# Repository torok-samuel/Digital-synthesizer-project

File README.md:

# Digital-synthesizer-project
Digital synthesizer project for university thesis.

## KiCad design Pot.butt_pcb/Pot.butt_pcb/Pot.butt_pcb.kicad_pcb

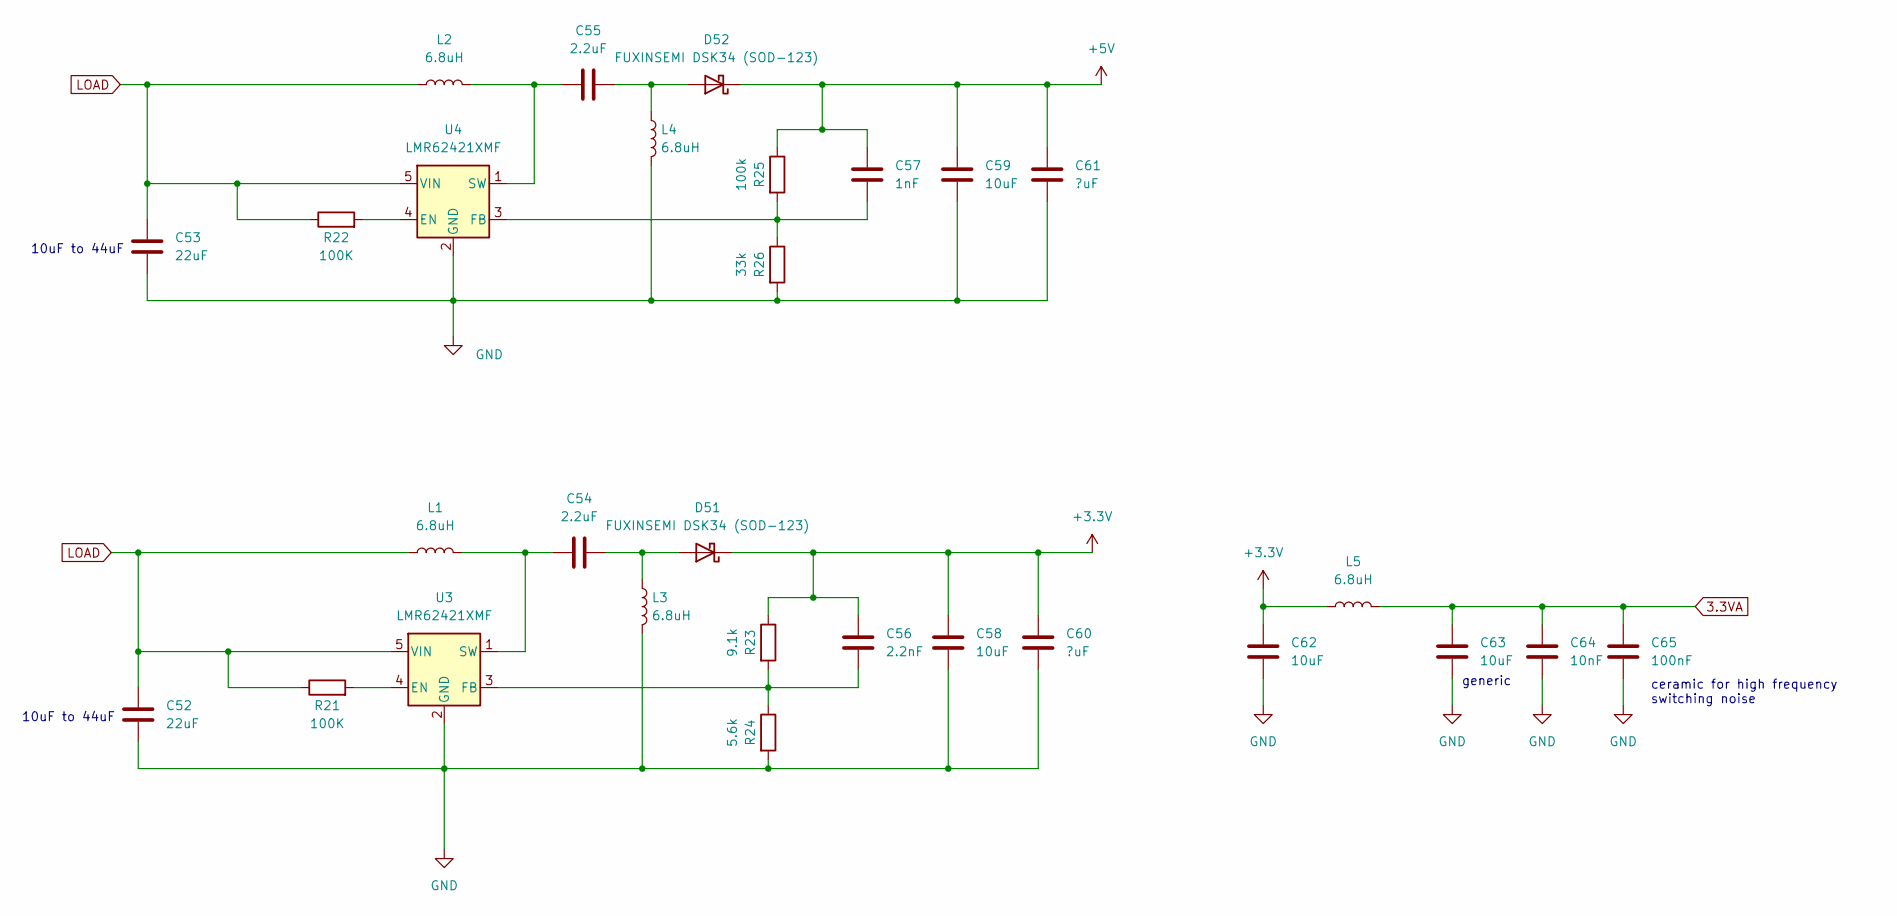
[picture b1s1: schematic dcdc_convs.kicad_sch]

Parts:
C52, C53: 22uF; C_0805_2012Metric_Pad1.18x1.45mm_HandSolder
C54, C55: 2.2uF; C_0805_2012Metric_Pad1.18x1.45mm_HandSolder
C56: 2.2nF; C_0805_2012Metric_Pad1.18x1.45mm_HandSolder
C57: 1nF; C_0805_2012Metric_Pad1.18x1.45mm_HandSolder
C58, C59, C62, C63: 10uF; C_0805_2012Metric_Pad1.18x1.45mm_HandSolder
C60, C61: ?uF; C_0805_2012Metric_Pad1.18x1.45mm_HandSolder
C64: 10nF; C_0805_2012Metric_Pad1.18x1.45mm_HandSolder
C65: 100nF; C_0805_2012Metric_Pad1.18x1.45mm_HandSolder
D51, D52: FUXINSEMI DSK34 (SOD-123); D_SOD-123
L1, L2, L3, L4, L5: 6.8uH; inductor_koherelec
R21, R22: 100K; R_0805_2012Metric_Pad1.20x1.40mm_HandSolder
R23: 9.1k; R_0805_2012Metric_Pad1.20x1.40mm_HandSolder
R24: 5.6k; R_0805_2012Metric_Pad1.20x1.40mm_HandSolder
R25: 100k; R_0805_2012Metric_Pad1.20x1.40mm_HandSolder
R26: 33k; R_0805_2012Metric_Pad1.20x1.40mm_HandSolder
U3, U4: LMR62421XMF; SOT-23-5

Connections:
3.3VA: C63.1, C64.1, C65.1, L5.2; also elsewhere on the board
+3V3: C56.1, C58.1, C60.1, C62.1, D51.1 (K), L5.1, R23.1; also elsewhere on the board
+5V: C57.1, C59.1, C61.1, D52.1 (K), R25.1; also elsewhere on the board
GND: C52.2, C53.2, C58.2, C59.2, C60.2, C61.2, C62.2, C63.2, C64.2, C65.2, L3.2, L4.2, R24.2, R26.2, U3.2 (GND), U4.2 (GND); also elsewhere on the board
LOAD: C52.1, C53.1, L1.1, L2.1, R21.1, R22.1, U3.5 (VIN), U4.5 (VIN); also elsewhere on the board
unnamed: C54.1, L1.2, U3.1 (SW)
unnamed: C54.2, D51.2 (A), L3.1
unnamed: C55.1, L2.2, U4.1 (SW)
unnamed: C55.2, D52.2 (A), L4.1
unnamed: C56.2, R23.2, R24.1, U3.3 (FB)
unnamed: C57.2, R25.2, R26.1, U4.3 (FB)
unnamed: R21.2, U3.4 (EN)
unnamed: R22.2, U4.4 (EN)

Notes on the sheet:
10uF to 44uF
generic
ceramic for high frequency switching noise

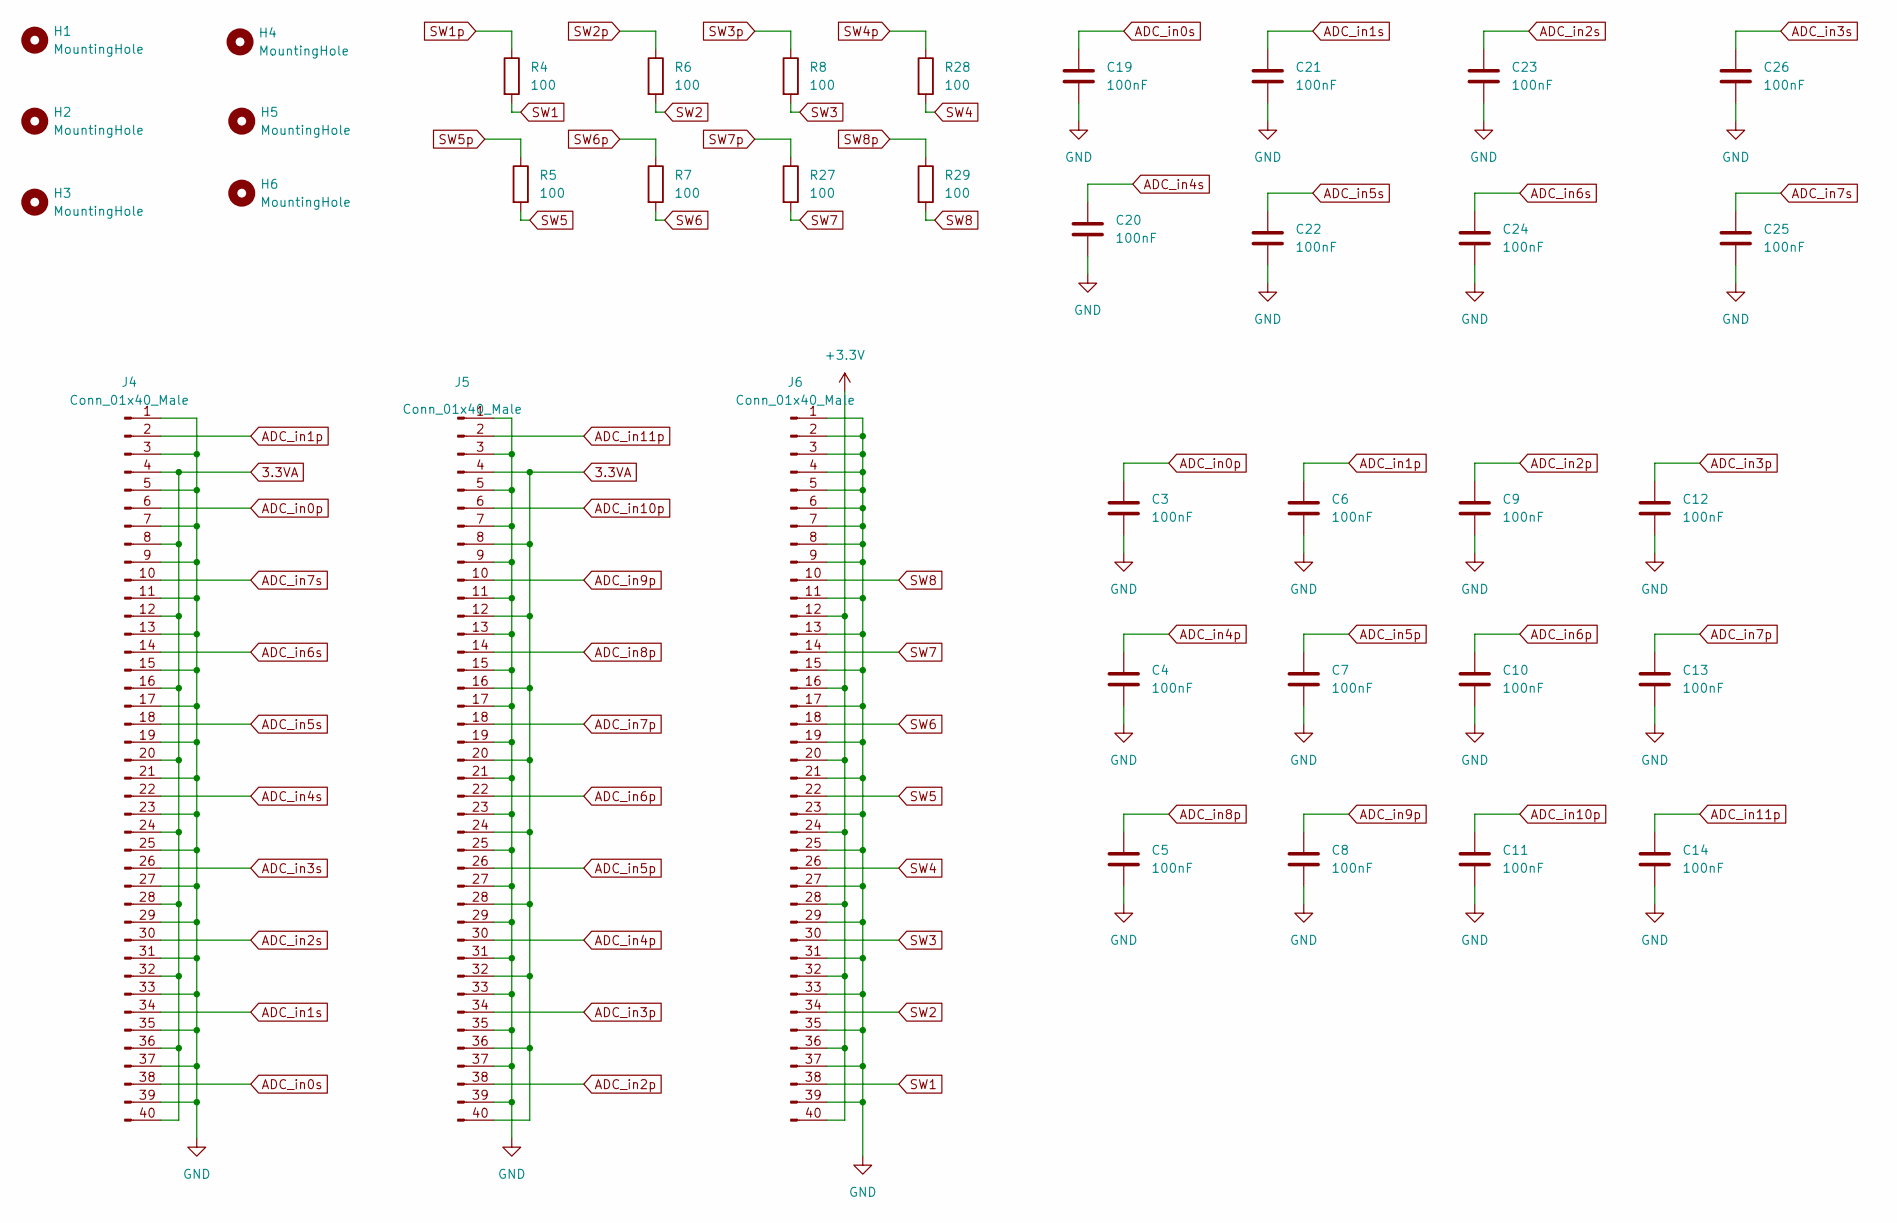
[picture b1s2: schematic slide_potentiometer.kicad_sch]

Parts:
C3, C4, C5, C6, C7, C8, C9, C10, C11, C12, C13, C14, C19, C20, C21, C22, C23, C24, C25, C26: 100nF; C_0805_2012Metric_Pad1.18x1.45mm_HandSolder
H1, H2, H3, H4, H5, H6: MountingHole; MountingHole_3.2mm_M3_Pad_Via
J4, J5, J6: Conn_01x40_Male; IDC-Header_2x20_P2.54mm_Vertical
R4, R5, R6, R7, R8, R27, R28, R29: 100; R_0805_2012Metric_Pad1.20x1.40mm_HandSolder

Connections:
3.3VA: J4.4, J4.8, J4.12, J4.16, J4.20, J4.24, J4.28, J4.32, J4.36, J4.40, J5.4, J5.8, J5.12, J5.16, J5.20, J5.24, J5.28, J5.32, J5.36, J5.40; also elsewhere on the board
+3V3: J6.12, J6.16, J6.20, J6.24, J6.28, J6.32, J6.36, J6.40; also elsewhere on the board
ADC_in0p: C3.1, J4.6; also elsewhere on the board
ADC_in0s: C19.1, J4.38; also elsewhere on the board
ADC_in1p: C6.1, J4.2; also elsewhere on the board
ADC_in1s: C21.1, J4.34; also elsewhere on the board
ADC_in2p: C9.1, J5.38; also elsewhere on the board
ADC_in2s: C23.1, J4.30; also elsewhere on the board
ADC_in3p: C12.1, J5.34; also elsewhere on the board
ADC_in3s: C26.1, J4.26; also elsewhere on the board
ADC_in4p: C4.1, J5.30; also elsewhere on the board
ADC_in4s: C20.1, J4.22; also elsewhere on the board
ADC_in5p: C7.1, J5.26; also elsewhere on the board
ADC_in5s: C22.1, J4.18; also elsewhere on the board
ADC_in6p: C10.1, J5.22; also elsewhere on the board
ADC_in6s: C24.1, J4.14; also elsewhere on the board
ADC_in7p: C13.1, J5.18; also elsewhere on the board
ADC_in7s: C25.1, J4.10; also elsewhere on the board
ADC_in8p: C5.1, J5.14; also elsewhere on the board
ADC_in9p: C8.1, J5.10; also elsewhere on the board
ADC_in10p: C11.1, J5.6; also elsewhere on the board
ADC_in11p: C14.1, J5.2; also elsewhere on the board
GND: C3.2, C4.2, C5.2, C6.2, C7.2, C8.2, C9.2, C10.2, C11.2, C12.2, C13.2, C14.2, C19.2, C20.2, C21.2, C22.2, C23.2, C24.2, C25.2, C26.2, J4.1, J4.3, J4.5, J4.7, J4.9, J4.11, J4.13, J4.15, J4.17, J4.19, J4.21, J4.23, J4.25, J4.27, J4.29, J4.31, J4.33, J4.35, J4.37, J4.39, J5.1, J5.3, J5.5, J5.7, J5.9, J5.11, J5.13, J5.15, J5.17, J5.19, J5.21, J5.23, J5.25, J5.27, J5.29, J5.31, J5.33, J5.35, J5.37, J5.39, J6.1, J6.2, J6.3, J6.4, J6.5, J6.6, J6.7, J6.8, J6.9, J6.11, J6.13, J6.15, J6.17, J6.19, J6.21, J6.23, J6.25, J6.27, J6.29, J6.31, J6.33, J6.35, J6.37, J6.39; also elsewhere on the board
SW1: J6.38, R4.2
SW1p: R4.1; also elsewhere on the board
SW2: J6.34, R6.2
SW2p: R6.1; also elsewhere on the board
SW3: J6.30, R8.2
SW3p: R8.1; also elsewhere on the board
SW4: J6.26, R28.2
SW4p: R28.1; also elsewhere on the board
SW5: J6.22, R5.2
SW5p: R5.1; also elsewhere on the board
SW6: J6.18, R7.2
SW6p: R7.1; also elsewhere on the board
SW7: J6.14, R27.2
SW7p: R27.1; also elsewhere on the board
SW8: J6.10, R29.2
SW8p: R29.1; also elsewhere on the board

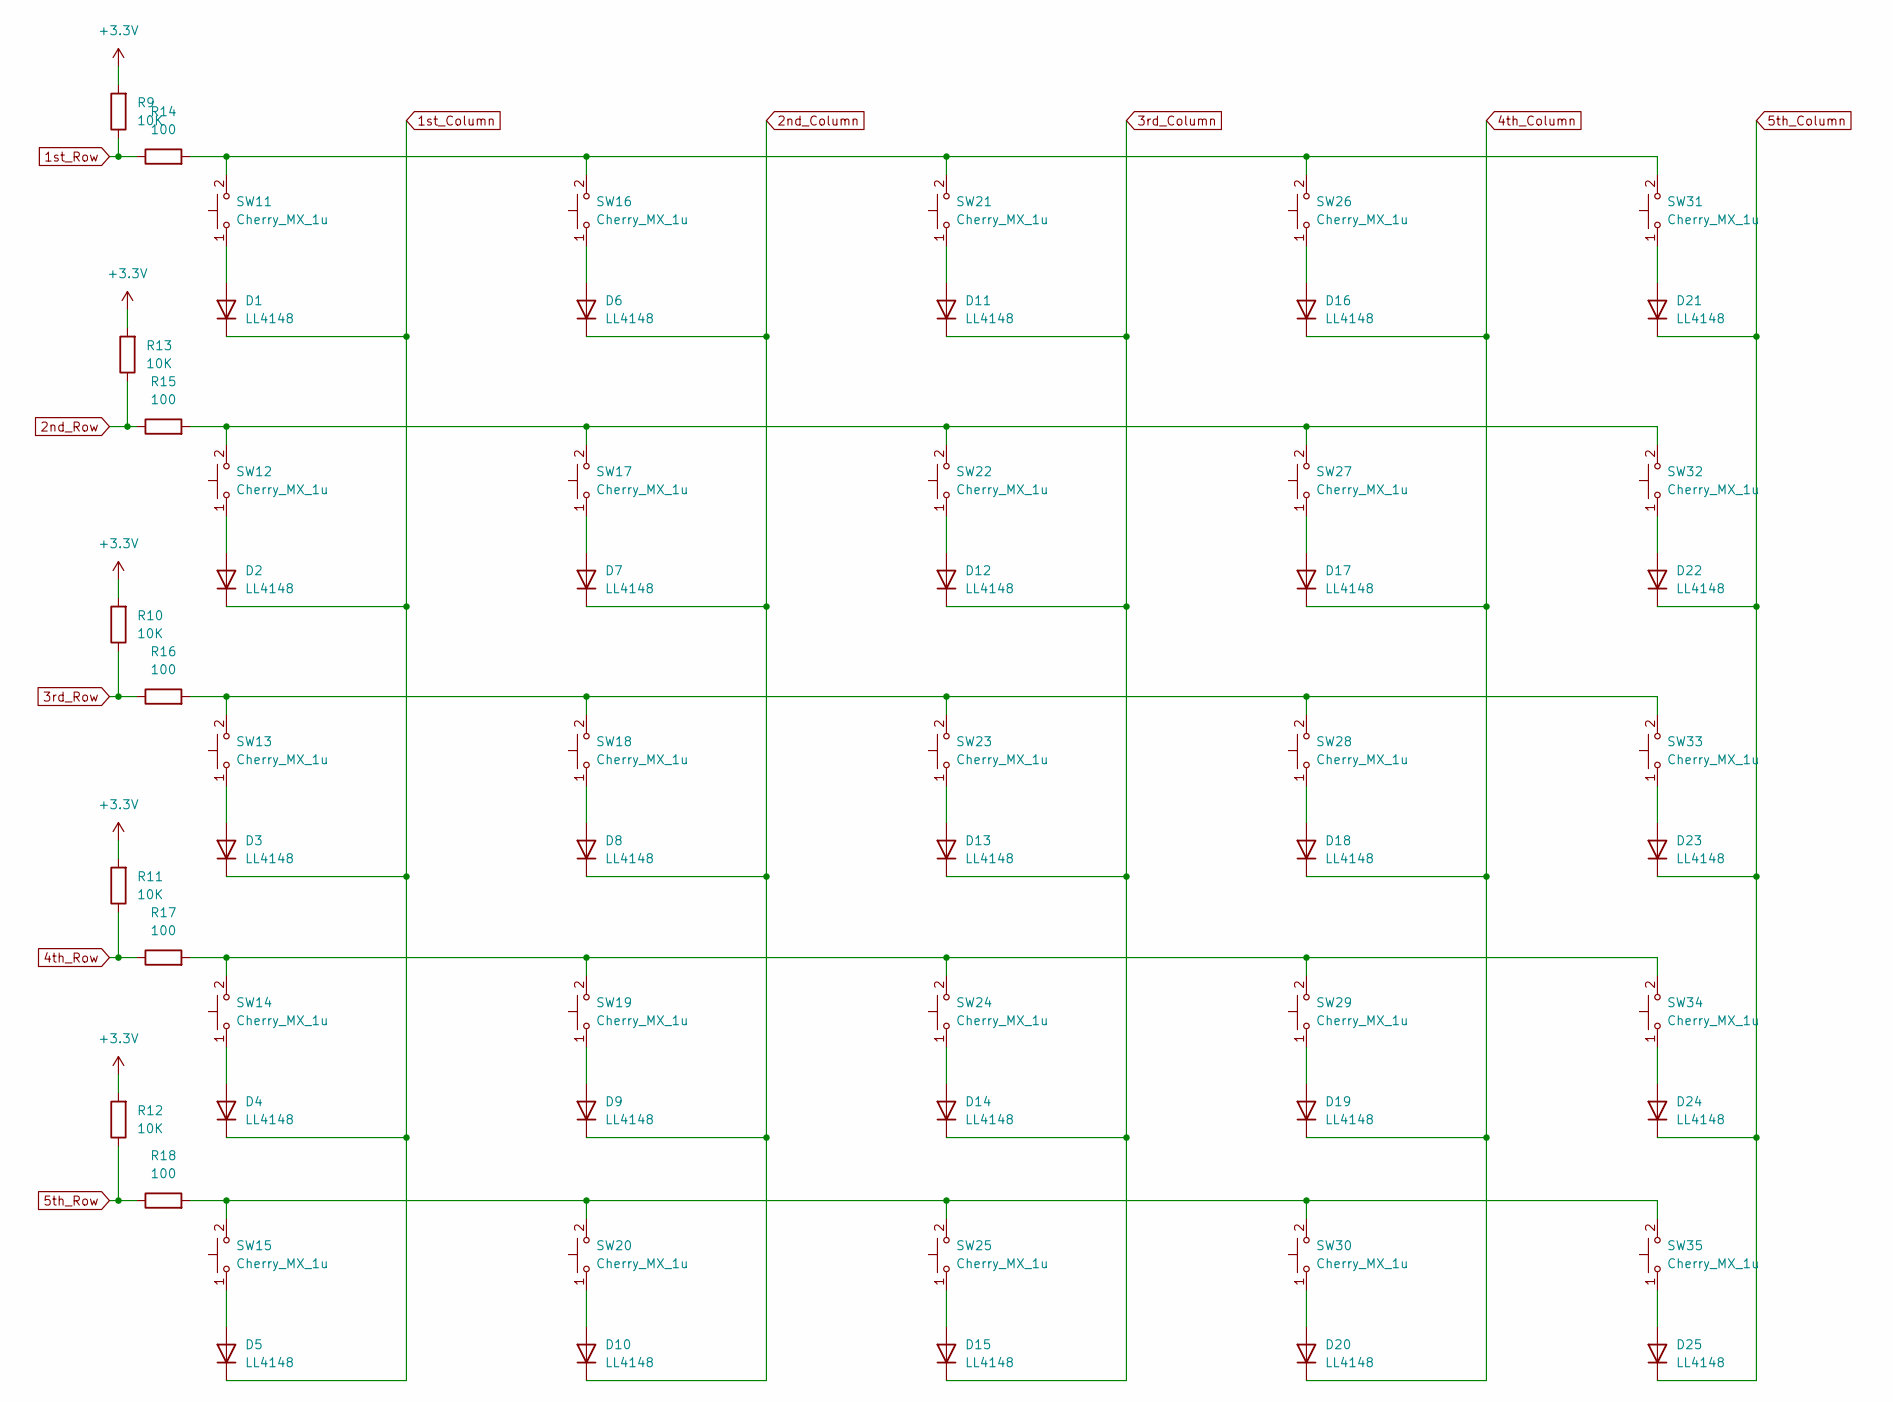
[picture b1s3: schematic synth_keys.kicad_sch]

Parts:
D1, D2, D3, D4, D5, D6, D7, D8, D9, D10, D11, D12, D13, D14, D15, D16, D17, D18, D19, D20, D21, D22, D23, D24, D25: LL4148; D_MiniMELF
R9, R10, R11, R12, R13: 10K; R_0805_2012Metric_Pad1.20x1.40mm_HandSolder
R14, R15, R16, R17, R18: 100; R_0805_2012Metric_Pad1.20x1.40mm_HandSolder
SW11, SW12, SW13, SW14, SW15, SW16, SW17, SW18, SW19, SW20, SW21, SW22, SW23, SW24, SW25, SW26, SW27, SW28, SW29, SW30, SW31, SW32, SW33, SW34, SW35: Cherry_MX_1u; SW_Cherry_MX_PCB_1.00u

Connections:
1st_Column: D1.1 (K), D2.1 (K), D3.1 (K), D4.1 (K), D5.1 (K); also elsewhere on the board
1st_Row: R9.1, R14.1; also elsewhere on the board
2nd_Column: D6.1 (K), D7.1 (K), D8.1 (K), D9.1 (K), D10.1 (K); also elsewhere on the board
2nd_Row: R13.1, R15.1; also elsewhere on the board
3rd_Column: D11.1 (K), D12.1 (K), D13.1 (K), D14.1 (K), D15.1 (K); also elsewhere on the board
3rd_Row: R10.1, R16.1; also elsewhere on the board
4th_Column: D16.1 (K), D17.1 (K), D18.1 (K), D19.1 (K), D20.1 (K); also elsewhere on the board
4th_Row: R11.1, R17.1; also elsewhere on the board
5th_Column: D21.1 (K), D22.1 (K), D23.1 (K), D24.1 (K), D25.1 (K); also elsewhere on the board
5th_Row: R12.1, R18.1; also elsewhere on the board
+3V3: R9.2, R10.2, R11.2, R12.2, R13.2; also elsewhere on the board
unnamed: D1.2 (A), SW11.1
unnamed: D2.2 (A), SW12.1
unnamed: D3.2 (A), SW13.1
unnamed: D4.2 (A), SW14.1
unnamed: D5.2 (A), SW15.1
unnamed: D6.2 (A), SW16.1
unnamed: D7.2 (A), SW17.1
unnamed: D8.2 (A), SW18.1
unnamed: D9.2 (A), SW19.1
unnamed: D10.2 (A), SW20.1
unnamed: D11.2 (A), SW21.1
unnamed: D12.2 (A), SW22.1
unnamed: D13.2 (A), SW23.1
unnamed: D14.2 (A), SW24.1
unnamed: D15.2 (A), SW25.1
unnamed: D16.2 (A), SW26.1
unnamed: D17.2 (A), SW27.1
unnamed: D18.2 (A), SW28.1
unnamed: D19.2 (A), SW29.1
unnamed: D20.2 (A), SW30.1
unnamed: D21.2 (A), SW31.1
unnamed: D22.2 (A), SW32.1
unnamed: D23.2 (A), SW33.1
unnamed: D24.2 (A), SW34.1
unnamed: D25.2 (A), SW35.1
unnamed: R14.2, SW11.2, SW16.2, SW21.2, SW26.2, SW31.2
unnamed: R15.2, SW12.2, SW17.2, SW22.2, SW27.2, SW32.2
unnamed: R16.2, SW13.2, SW18.2, SW23.2, SW28.2, SW33.2
unnamed: R17.2, SW14.2, SW19.2, SW24.2, SW29.2, SW34.2
unnamed: R18.2, SW15.2, SW20.2, SW25.2, SW30.2, SW35.2

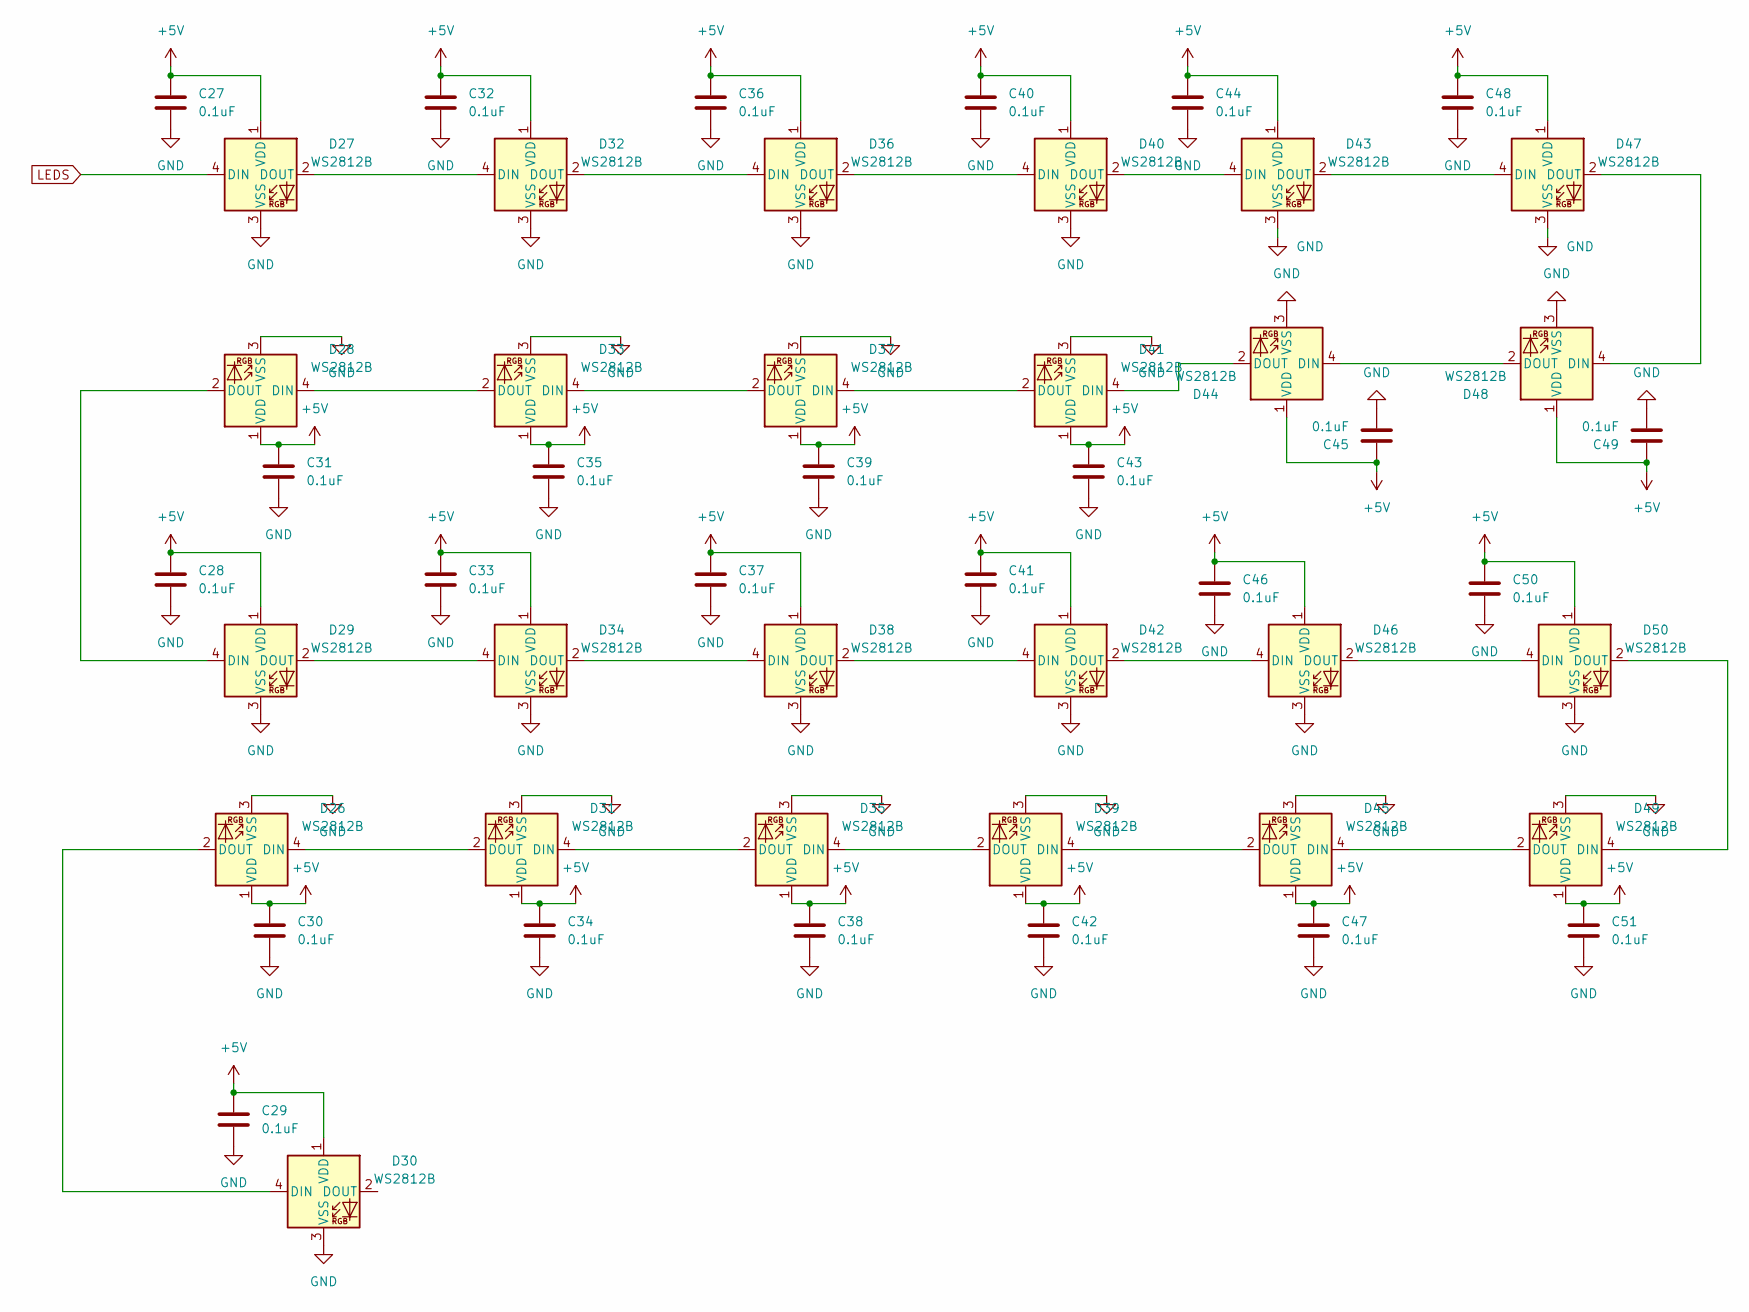
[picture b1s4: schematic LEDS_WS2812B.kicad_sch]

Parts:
C27, C28, C29, C30, C31, C32, C33, C34, C35, C36, C37, C38, C39, C40, C41, C42, C43, C44, C45, C46, C47, C48, C49, C50, C51: 0.1uF; C_0805_2012Metric_Pad1.18x1.45mm_HandSolder
D26, D27, D28, D29, D30, D31, D32, D33, D34, D35, D36, D37, D38, D39, D40, D41, D42, D43, D44, D45, D46, D47, D48, D49, D50: WS2812B; LED_WS2812B_PLCC4_5.0x5.0mm_P3.2mm

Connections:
+5V: C27.1, C28.1, C29.1, C30.1, C31.1, C32.1, C33.1, C34.1, C35.1, C36.1, C37.1, C38.1, C39.1, C40.1, C41.1, C42.1, C43.1, C44.1, C45.1, C46.1, C47.1, C48.1, C49.1, C50.1, C51.1, D26.1 (VDD), D27.1 (VDD), D28.1 (VDD), D29.1 (VDD), D30.1 (VDD), D31.1 (VDD), D32.1 (VDD), D33.1 (VDD), D34.1 (VDD), D35.1 (VDD), D36.1 (VDD), D37.1 (VDD), D38.1 (VDD), D39.1 (VDD), D40.1 (VDD), D41.1 (VDD), D42.1 (VDD), D43.1 (VDD), D44.1 (VDD), D45.1 (VDD), D46.1 (VDD), D47.1 (VDD), D48.1 (VDD), D49.1 (VDD), D50.1 (VDD); also elsewhere on the board
GND: C27.2, C28.2, C29.2, C30.2, C31.2, C32.2, C33.2, C34.2, C35.2, C36.2, C37.2, C38.2, C39.2, C40.2, C41.2, C42.2, C43.2, C44.2, C45.2, C46.2, C47.2, C48.2, C49.2, C50.2, C51.2, D26.3 (VSS), D27.3 (VSS), D28.3 (VSS), D29.3 (VSS), D30.3 (VSS), D31.3 (VSS), D32.3 (VSS), D33.3 (VSS), D34.3 (VSS), D35.3 (VSS), D36.3 (VSS), D37.3 (VSS), D38.3 (VSS), D39.3 (VSS), D40.3 (VSS), D41.3 (VSS), D42.3 (VSS), D43.3 (VSS), D44.3 (VSS), D45.3 (VSS), D46.3 (VSS), D47.3 (VSS), D48.3 (VSS), D49.3 (VSS), D50.3 (VSS); also elsewhere on the board
LEDS: D27.4 (DIN); also elsewhere on the board
unnamed: D26.2 (DOUT), D30.4 (DIN)
unnamed: D26.4 (DIN), D31.2 (DOUT)
unnamed: D27.2 (DOUT), D32.4 (DIN)
unnamed: D28.2 (DOUT), D29.4 (DIN)
unnamed: D28.4 (DIN), D33.2 (DOUT)
unnamed: D29.2 (DOUT), D34.4 (DIN)
unnamed: D31.4 (DIN), D35.2 (DOUT)
unnamed: D32.2 (DOUT), D36.4 (DIN)
unnamed: D33.4 (DIN), D37.2 (DOUT)
unnamed: D34.2 (DOUT), D38.4 (DIN)
unnamed: D35.4 (DIN), D39.2 (DOUT)
unnamed: D36.2 (DOUT), D40.4 (DIN)
unnamed: D37.4 (DIN), D41.2 (DOUT)
unnamed: D38.2 (DOUT), D42.4 (DIN)
unnamed: D39.4 (DIN), D45.2 (DOUT)
unnamed: D40.2 (DOUT), D43.4 (DIN)
unnamed: D41.4 (DIN), D44.2 (DOUT)
unnamed: D42.2 (DOUT), D46.4 (DIN)
unnamed: D43.2 (DOUT), D47.4 (DIN)
unnamed: D44.4 (DIN), D48.2 (DOUT)
unnamed: D45.4 (DIN), D49.2 (DOUT)
unnamed: D46.2 (DOUT), D50.4 (DIN)
unnamed: D47.2 (DOUT), D48.4 (DIN)
unnamed: D49.4 (DIN), D50.2 (DOUT)

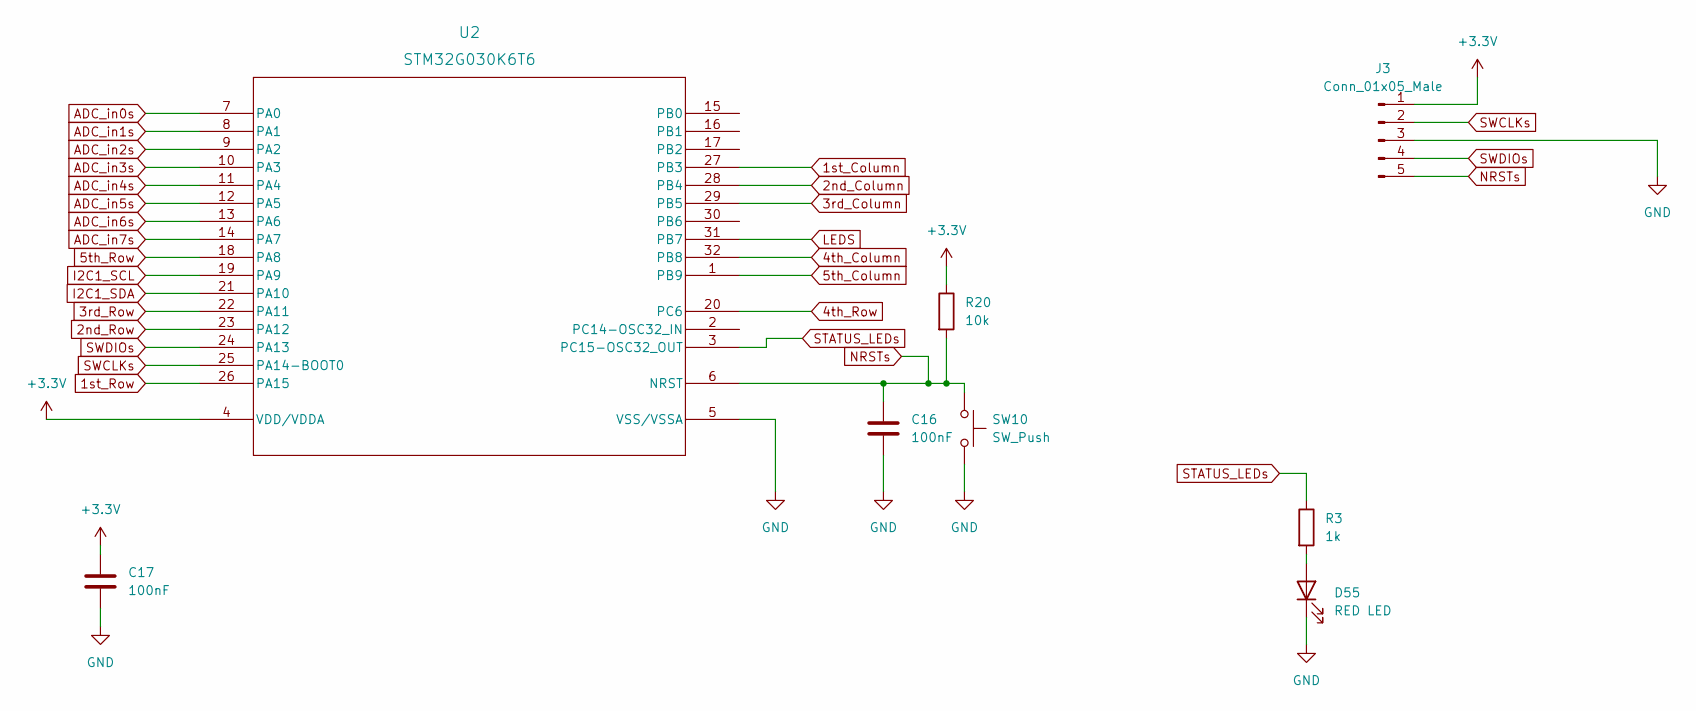
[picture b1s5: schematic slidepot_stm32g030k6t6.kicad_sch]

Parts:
C16, C17: 100nF; C_0805_2012Metric_Pad1.18x1.45mm_HandSolder
D55: RED LED; LED_0805_2012Metric_Pad1.15x1.40mm_HandSolder
J3: Conn_01x05_Male; PinSocket_1x05_P2.54mm_Horizontal
R3: 1k; R_0805_2012Metric_Pad1.20x1.40mm_HandSolder
R20: 10k; R_0805_2012Metric_Pad1.20x1.40mm_HandSolder
SW10: SW_Push; ROCPU Switches TP10721645
U2: STM32G030K6T6; LQFP-32

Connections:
1st_Column: U2.27 (PB3); also elsewhere on the board
1st_Row: U2.26 (PA15); also elsewhere on the board
2nd_Column: U2.28 (PB4); also elsewhere on the board
2nd_Row: U2.23 (PA12); also elsewhere on the board
3rd_Column: U2.29 (PB5); also elsewhere on the board
3rd_Row: U2.22 (PA11); also elsewhere on the board
4th_Column: U2.32 (PB8); also elsewhere on the board
4th_Row: U2.20 (PC6); also elsewhere on the board
5th_Column: U2.1 (PB9); also elsewhere on the board
5th_Row: U2.18 (PA8); also elsewhere on the board
+3V3: C17.1, J3.1, R20.1, U2.4 (VDD/VDDA); also elsewhere on the board
ADC_in0s: U2.7 (PA0); also elsewhere on the board
ADC_in1s: U2.8 (PA1); also elsewhere on the board
ADC_in2s: U2.9 (PA2); also elsewhere on the board
ADC_in3s: U2.10 (PA3); also elsewhere on the board
ADC_in4s: U2.11 (PA4); also elsewhere on the board
ADC_in5s: U2.12 (PA5); also elsewhere on the board
ADC_in6s: U2.13 (PA6); also elsewhere on the board
ADC_in7s: U2.14 (PA7); also elsewhere on the board
GND: C16.2, C17.2, D55.1 (K), J3.3, SW10.2, U2.5 (VSS/VSSA); also elsewhere on the board
I2C1_SCL: U2.19 (PA9); also elsewhere on the board
I2C1_SDA: U2.21 (PA10); also elsewhere on the board
LEDS: U2.31 (PB7); also elsewhere on the board
NRSTs: C16.1, J3.5, R20.2, SW10.1, U2.6 (NRST)
unnamed: D55.2 (A), R3.2
STATUS_LEDs: R3.1, U2.3 (PC15-OSC32_OUT)
SWCLKs: J3.2, U2.25 (PA14-BOOT0)
SWDIOs: J3.4, U2.24 (PA13)

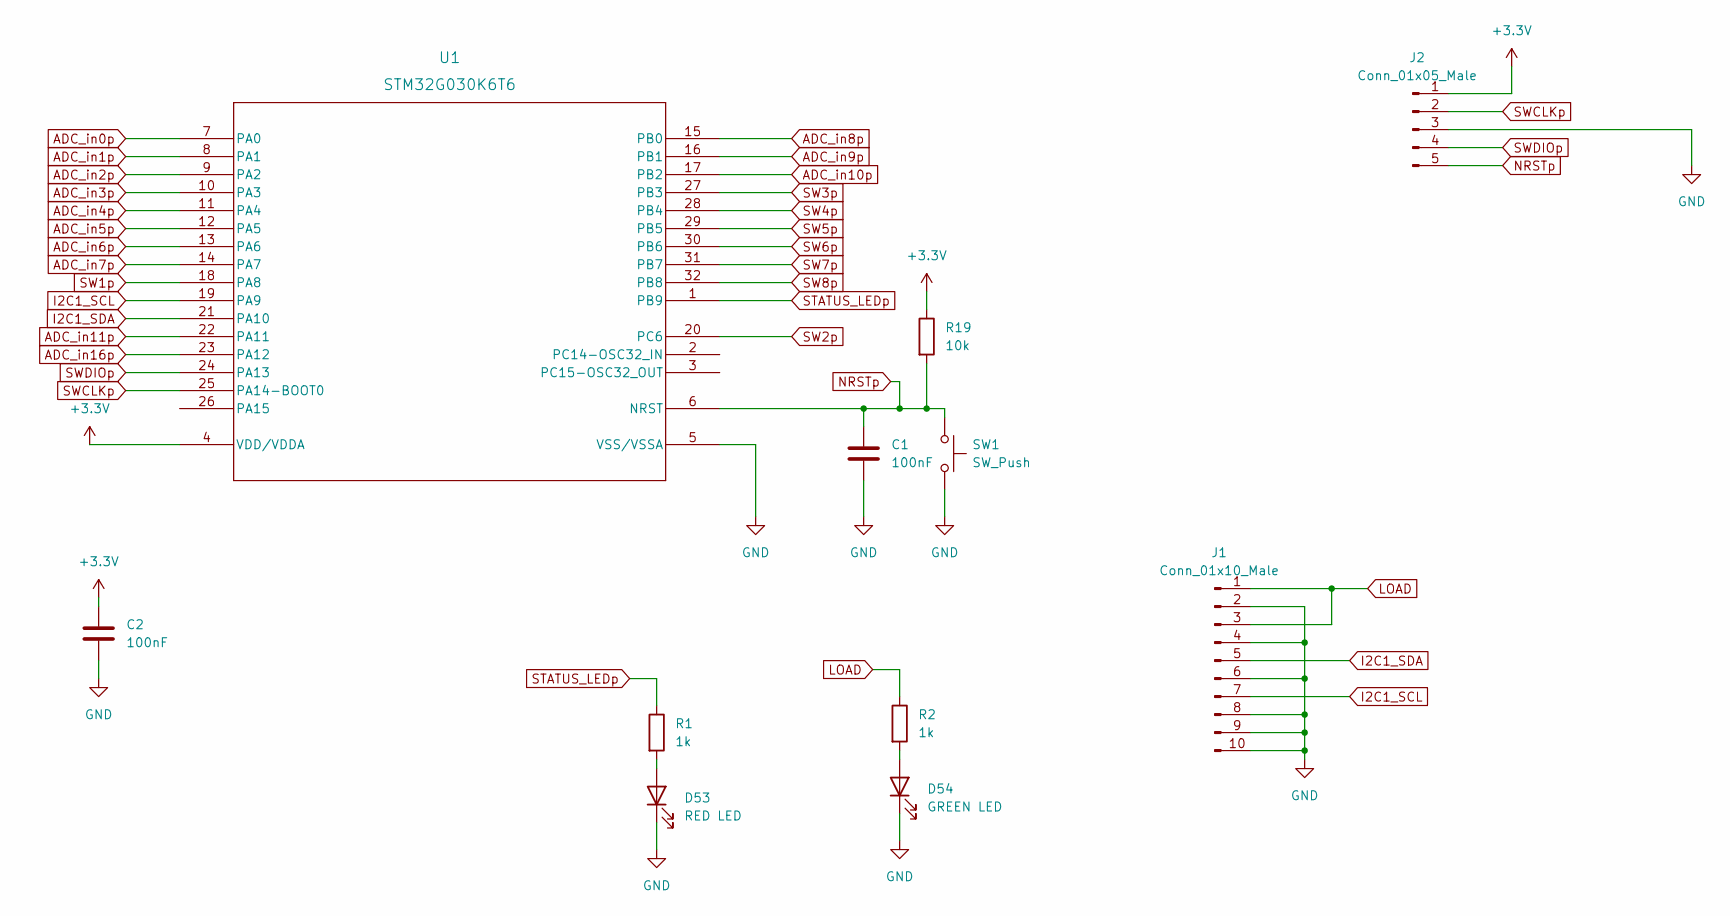
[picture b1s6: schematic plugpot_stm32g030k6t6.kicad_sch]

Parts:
C1, C2: 100nF; C_0805_2012Metric_Pad1.18x1.45mm_HandSolder
D53: RED LED; LED_0805_2012Metric_Pad1.15x1.40mm_HandSolder
D54: GREEN LED; LED_0805_2012Metric_Pad1.15x1.40mm_HandSolder
J1: Conn_01x10_Male; IDC-Header_2x05_P2.54mm_Horizontal
J2: Conn_01x05_Male; PinSocket_1x05_P2.54mm_Horizontal
R1, R2: 1k; R_0805_2012Metric_Pad1.20x1.40mm_HandSolder
R19: 10k; R_0805_2012Metric_Pad1.20x1.40mm_HandSolder
SW1: SW_Push; ROCPU Switches TP10721645
U1: STM32G030K6T6; LQFP-32

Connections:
+3V3: C2.1, J2.1, R19.1, U1.4 (VDD/VDDA); also elsewhere on the board
ADC_in0p: U1.7 (PA0); also elsewhere on the board
ADC_in1p: U1.8 (PA1); also elsewhere on the board
ADC_in2p: U1.9 (PA2); also elsewhere on the board
ADC_in3p: U1.10 (PA3); also elsewhere on the board
ADC_in4p: U1.11 (PA4); also elsewhere on the board
ADC_in5p: U1.12 (PA5); also elsewhere on the board
ADC_in6p: U1.13 (PA6); also elsewhere on the board
ADC_in7p: U1.14 (PA7); also elsewhere on the board
ADC_in8p: U1.15 (PB0); also elsewhere on the board
ADC_in9p: U1.16 (PB1); also elsewhere on the board
ADC_in10p: U1.17 (PB2); also elsewhere on the board
ADC_in11p: U1.22 (PA11); also elsewhere on the board
ADC_in16p: U1.23 (PA12)
GND: C1.2, C2.2, D53.1 (K), D54.1 (K), J1.2, J1.4, J1.6, J1.8, J1.9, J1.10, J2.3, SW1.2, U1.5 (VSS/VSSA); also elsewhere on the board
I2C1_SCL: J1.7, U1.19 (PA9); also elsewhere on the board
I2C1_SDA: J1.5, U1.21 (PA10); also elsewhere on the board
LOAD: J1.1, J1.3, R2.1; also elsewhere on the board
NRSTp: C1.1, J2.5, R19.2, SW1.1, U1.6 (NRST)
unnamed: D53.2 (A), R1.2
unnamed: D54.2 (A), R2.2
STATUS_LEDp: R1.1, U1.1 (PB9)
SW1p: U1.18 (PA8); also elsewhere on the board
SW2p: U1.20 (PC6); also elsewhere on the board
SW3p: U1.27 (PB3); also elsewhere on the board
SW4p: U1.28 (PB4); also elsewhere on the board
SW5p: U1.29 (PB5); also elsewhere on the board
SW6p: U1.30 (PB6); also elsewhere on the board
SW7p: U1.31 (PB7); also elsewhere on the board
SW8p: U1.32 (PB8); also elsewhere on the board
SWCLKp: J2.2, U1.25 (PA14-BOOT0)
SWDIOp: J2.4, U1.24 (PA13)

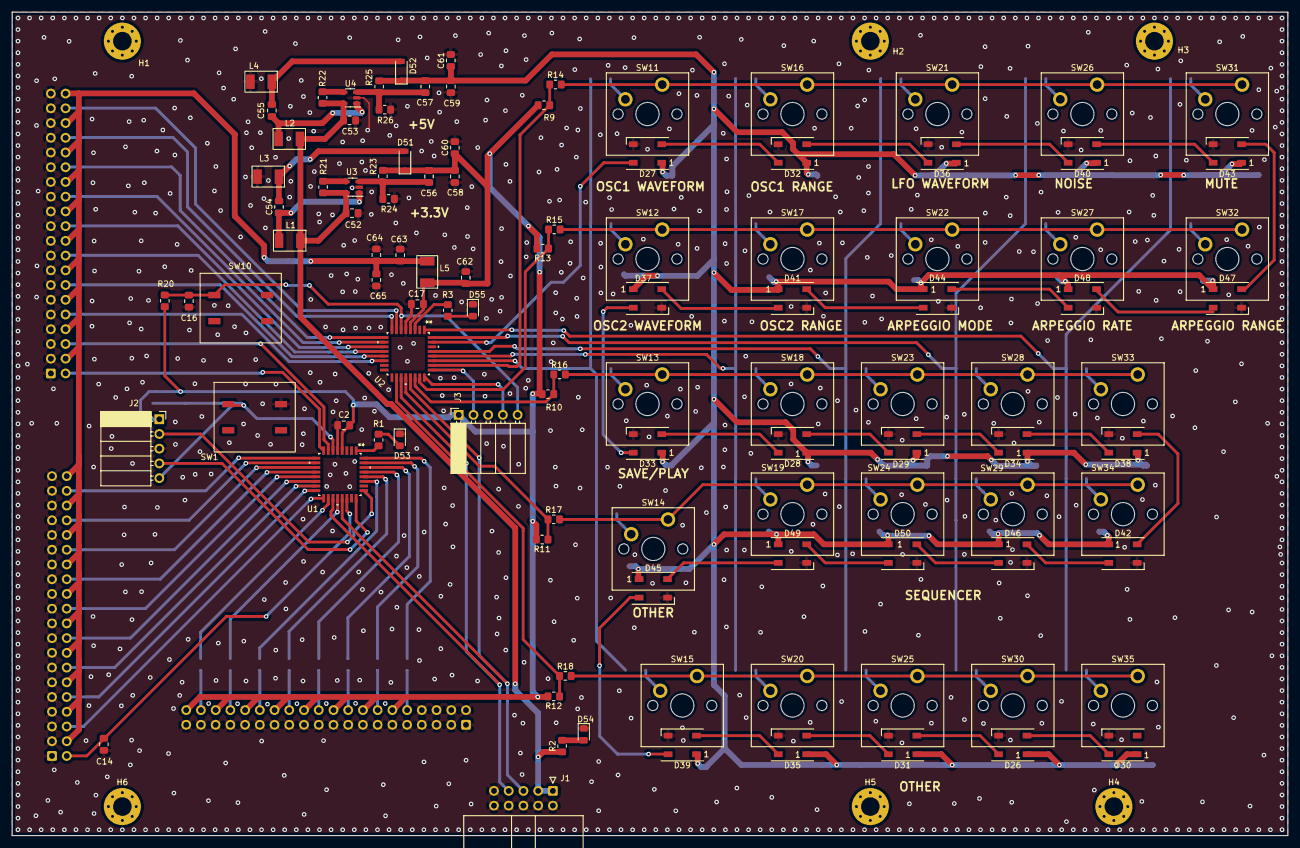
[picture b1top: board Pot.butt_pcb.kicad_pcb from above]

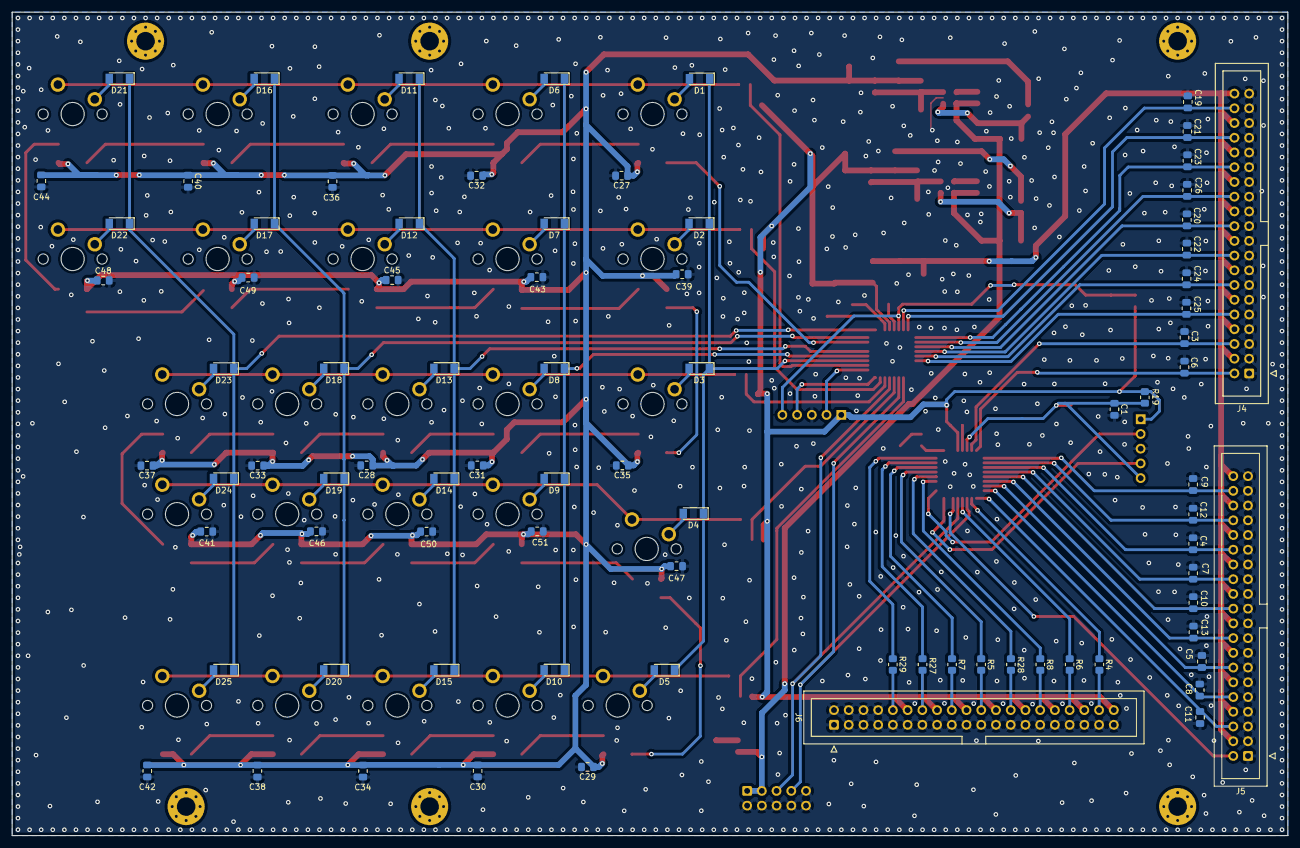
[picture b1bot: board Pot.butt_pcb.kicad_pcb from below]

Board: 2 copper layers, 220.0 x 142.0 mm, 195 parts (82 on the bottom side), 127 nets.
